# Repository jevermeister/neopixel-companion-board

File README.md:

# Neopixel companion board

This is a board to control and power Neopixels (WS2812 and derivatives) using a separate microcontroller.

**Please note that the board doesn't feature any fuses to keep it compact. If for whichever reasons you get a short, bad things may happen!
If in doubt, add a 5A fuse after the microfit connector for additional safety**

To reliably control and power also large strips, the board does a couple of things:

* A 1000uF capacitor for each strip to buffer initial power spikes which may cause the Neopixel controller to brownout due to voltage drops (which would cause the strip to now show anything)
* A 4.7k pulldown resistor for each microcontroller pin to make sure these pins are not floating. While most microcontrollers have integrated pulldowns which could be activated, this won't hurt and ensure a stable communication.
* A level shifter (SN74AHCT125D) as Neopixel expect 5V logic levels while most 32-bit microcontrollers have only 3.3V. Often they also work with 3.3V voltage but not always, that is why we make sure they will with a level shifter. In case you already have 5V logic level - This won't hurt at least and the level shifter is able to deal with it.
* Provide high current connectors. Each strip is connected using Molex Microfit 3.0 connectors which are rated up to 5A. The board itself is connected with screw terminals rated up to 18A.

I already put LCSC/JLCPCB part numbers in the design so you should be able to order these either assembled or know which parts to get.
Please note that I used a TE 796949-2 screw terminal on my PCB which is not available at LCSC so the one I put in there should also fit and work but I didn't test it.

How to wire it:
* Attach microcontroller pins to the JST-XH terminal labeled 1 2 3 4, these correspond to the J1 to J4 molex connectors

Best case those are pins which go straight to the microcontrollers without anything in between. I used PE7 to PE10 located at the EXP1 connector of my BigTreeTech Octopus Pro 1.0
* Attach a 5V power supply (don't try anything higher or the capacitors *will* pop) to the screw terminals, polarity is shown on the board

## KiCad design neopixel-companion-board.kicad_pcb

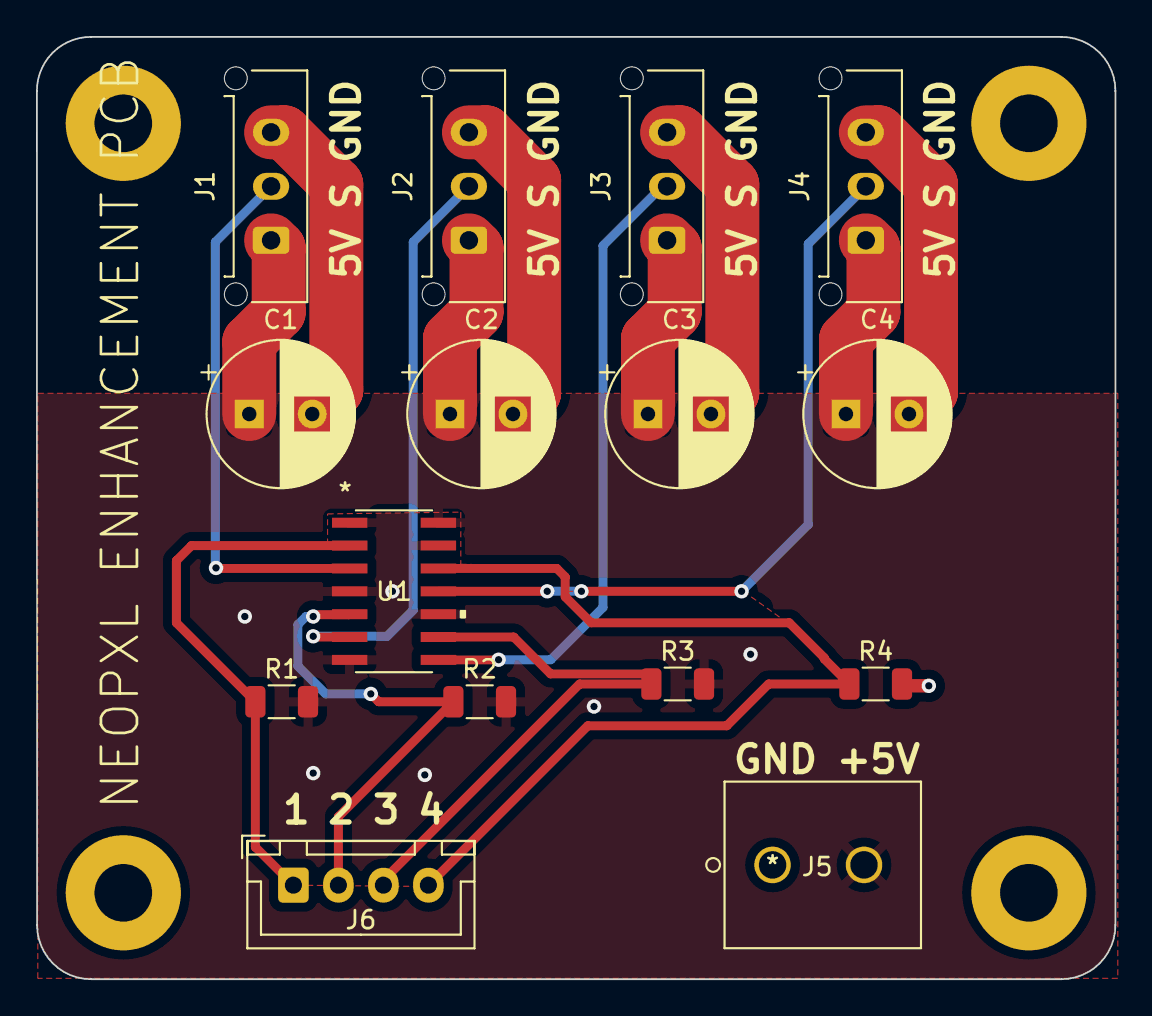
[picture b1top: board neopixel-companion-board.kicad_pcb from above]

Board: 2 copper layers, 59.9 x 52.4 mm, 15 parts (0 on the bottom side), 10 nets.

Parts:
C1, C2, C3, C4: 1000 uF; CP_Radial_D8.0mm_P3.50mm
J1: PXL_1_Output; Molex_Micro-Fit_3.0_43650-0315_1x03_P3.00mm_Vertical
J2: PXL_2_Output; Molex_Micro-Fit_3.0_43650-0315_1x03_P3.00mm_Vertical
J3: PXL_3_Output; Molex_Micro-Fit_3.0_43650-0315_1x03_P3.00mm_Vertical
J4: PXL_4_Output; Molex_Micro-Fit_3.0_43650-0315_1x03_P3.00mm_Vertical
J5: VIN; 796949-2
J6: PXL_Input; JST_XH_B4B-XH-A_1x04_P2.50mm_Vertical
R1, R2, R3, R4: 4.7K; R_1206_3216Metric
U1: SN74AHCT125D

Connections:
+5V: C1.1, C2.1, C3.1, C4.1, J1.1, J2.1, J3.1, J4.1, J5.2, U1.14 (VCC)
GND: C1.2, C2.2, C3.2, C4.2, J1.3, J2.3, J3.3, J4.3, J5.1, R1.2, R2.2, R3.2, R4.2, U1.1 (*1OE), U1.4 (*2OE), U1.7 (GND), U1.10 (*3OE), U1.13 (*4OE)
Neopixel_1: J6.1, R1.1, U1.2 (1A)
Neopixel_1_5V: J1.2, U1.3 (1Y)
Neopixel_2: J6.2, R2.1, U1.5 (2A)
Neopixel_2_5V: J2.2, U1.6 (2Y)
Neopixel_3: J6.3, R3.1, U1.9 (3A)
Neopixel_3_5V: J3.2, U1.8 (3Y)
Neopixel_4: J6.4, R4.1, U1.12 (4A)
Neopixel_4_5V: J4.2, U1.11 (4Y)

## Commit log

2023-02-24 Moved location
2023-03-03 initial beta stuff
2023-03-03 Added molex connector models and text
2023-03-03 Changed connector and added library files
2023-03-04 Replaced single schmitt triggers with a 4 bit level shifter
2023-04-11 Added LCSC parts and gerbers
2023-04-12 Added LCSC part numbers
2023-04-12 Create LICENSE

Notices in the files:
parts and their libraries:
Copyright 2021 Accelerated Designs. All rights reserved.
